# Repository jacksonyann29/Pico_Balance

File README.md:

# Pico_Balance
General Purpose Robot PCB with 2 motor drivers, IMU and appropriate power management for 9-24v. Intended to be used standalone or alongside an SBC depending on robotics application.

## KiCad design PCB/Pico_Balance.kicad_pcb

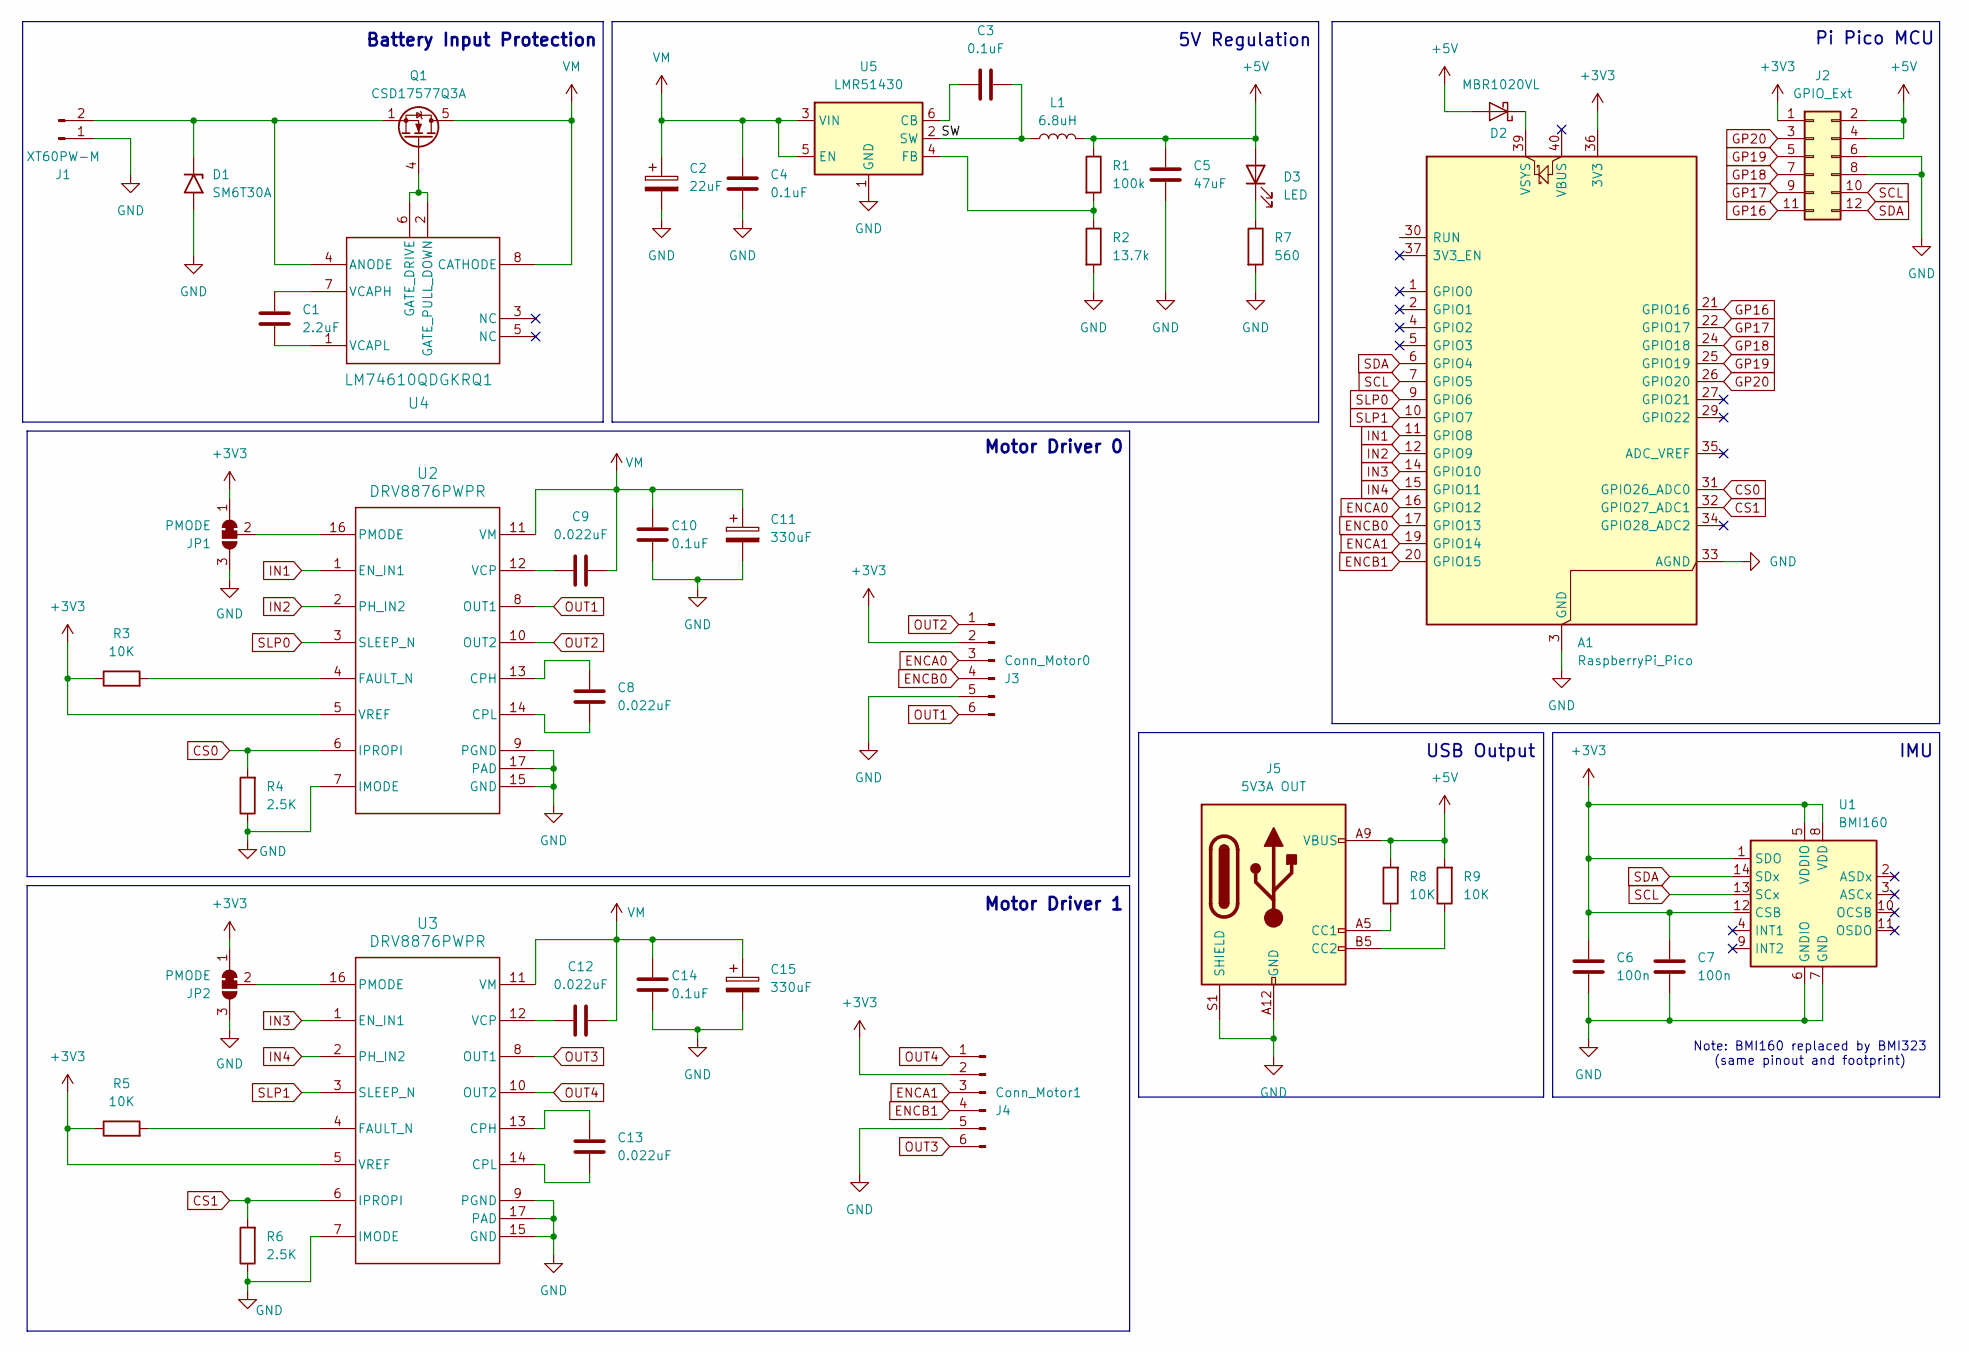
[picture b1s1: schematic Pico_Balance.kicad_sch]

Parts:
A1: RaspberryPi_Pico; RaspberryPi_Pico_Common_Unspecified
C1: 2.2uF; C_1206_3216Metric
C2: 22uF; CP_Elec_5x5.4
C3, C4, C10, C14: 0.1uF; C_0603_1608Metric
C5: 47uF; C_1210_3225Metric
C6, C7: 100n; C_0603_1608Metric
C8, C9, C12, C13: 0.022uF; C_0603_1608Metric
C11, C15: 330uF; CP_Elec_10x10.5
D1: SM6T30A; D_SMB
D2: MBR1020VL; D_SOD-123F
D3: LED; LED_0805_2012Metric
J1: XT60PW-M; AMASS_XT60PW-M_1x02_P7.20mm_Horizontal
J2: GPIO_Ext; PinHeader_2x06_P2.54mm_Vertical
J3: Conn_Motor0; PinSocket_1x06_P2.54mm_Vertical
J4: Conn_Motor1; PinSocket_1x06_P2.54mm_Vertical
J5: 5V3A OUT; USB_C_Receptacle_HRO_TYPE-C-31-M-17
JP1, JP2: PMODE; SolderJumper-3_P1.3mm_Bridged12_Pad1.0x1.5mm_NumberLabels
L1: 6.8uH; L_APV_APH0630
Q1: CSD17577Q3A; VSON-8_3.3x3.3mm_P0.65mm_NexFET
R1: 100k; R_0603_1608Metric
R2: 13.7k; R_0603_1608Metric
R3, R5, R8, R9: 10K; R_0603_1608Metric
R4, R6: 2.5K; R_0603_1608Metric
R7: 560; R_0603_1608Metric
U1: BMI160; Bosch_LGA-14_3x2.5mm_P0.5mm
U2, U3: DRV8876PWPR; PWP0016J_N
U4: LM74610QDGKRQ1; DGK0008A_N
U5: LMR51430; SOT-23-6

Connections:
+3V3: A1.36 (3V3), C6.1, C7.1, J2.1, J3.2, J4.2, JP1.1 (A), JP2.1 (A), R3.1, R5.1, U1.1 (SDO), U1.5 (VDDIO), U1.8 (VDD), U1.12 (CSB), U2.5 (VREF), U3.5 (VREF)
+5V: C5.1, D2.2 (A), D3.2 (A), J2.2, J2.4, J5.A9 (VBUS), J5.B9 (VBUS), L1.2, R1.1, R8.2, R9.2
/SW: C3.2, L1.1, U5.2 (SW)
CS0: A1.31 (GPIO26_ADC0), R4.2, U2.6 (IPROPI)
CS1: A1.32 (GPIO27_ADC1), R6.2, U3.6 (IPROPI)
ENCA0: A1.16 (GPIO12), J3.3
ENCA1: A1.19 (GPIO14), J4.3
ENCB0: A1.17 (GPIO13), J3.4
ENCB1: A1.20 (GPIO15), J4.4
GND: A1.3 (GND), A1.8 (GND), A1.13 (GND), A1.18 (GND), A1.23 (GND), A1.28 (GND), A1.33 (AGND), A1.38 (GND), C2.2, C4.2, C5.2, C6.2, C7.2, C10.2, C11.2, C14.2, C15.2, D1.2 (A2), J1.1, J2.6, J2.8, J3.5, J4.5, J5.A12 (GND), J5.B12 (GND), J5.S1 (SHIELD), JP1.3 (B), JP2.3 (B), R2.2, R4.1, R6.1, R7.2, U1.6 (GNDIO), U1.7 (GND), U2.7 (IMODE), U2.9 (PGND), U2.15 (GND), U2.17 (PAD), U3.7 (IMODE), U3.9 (PGND), U3.15 (GND), U3.17 (PAD), U5.1 (GND)
GP16: A1.21 (GPIO16), J2.11
GP17: A1.22 (GPIO17), J2.9
GP18: A1.24 (GPIO18), J2.7
GP19: A1.25 (GPIO19), J2.5
GP20: A1.26 (GPIO20), J2.3
IN1: A1.11 (GPIO8), U2.1 (EN_IN1)
IN2: A1.12 (GPIO9), U2.2 (PH_IN2)
IN3: A1.14 (GPIO10), U3.1 (EN_IN1)
IN4: A1.15 (GPIO11), U3.2 (PH_IN2)
unnamed: A1.39 (VSYS), D2.1 (K)
unnamed: D1.1 (A1), J1.2, Q1.1 (S), Q1.2 (S), Q1.3 (S), U4.4 (ANODE)
unnamed: D3.1 (K), R7.1
unnamed: J5.A5 (CC1), R8.1
unnamed: J5.B5 (CC2), R9.1
unnamed: JP1.2 (C), U2.16 (PMODE)
unnamed: JP2.2 (C), U3.16 (PMODE)
unnamed: Q1.4 (G), U4.2 (GATE_PULL_DOWN), U4.6 (GATE_DRIVE)
unnamed: C8.1, U2.13 (CPH)
unnamed: C8.2, U2.14 (CPL)
unnamed: R3.2, U2.4 (FAULT_N)
unnamed: C9.1, U2.12 (VCP)
unnamed: C13.1, U3.13 (CPH)
unnamed: C13.2, U3.14 (CPL)
unnamed: R5.2, U3.4 (FAULT_N)
unnamed: C12.1, U3.12 (VCP)
unnamed: C1.1, U4.7 (VCAPH)
unnamed: C1.2, U4.1 (VCAPL)
unnamed: C3.1, U5.6 (CB)
unnamed: R1.2, R2.1, U5.4 (FB)
OUT1: J3.6, U2.8 (OUT1)
OUT2: J3.1, U2.10 (OUT2)
OUT3: J4.6, U3.8 (OUT1)
OUT4: J4.1, U3.10 (OUT2)
SCL: A1.7 (GPIO5), J2.10, U1.13 (SCx)
SDA: A1.6 (GPIO4), J2.12, U1.14 (SDx)
SLP0: A1.9 (GPIO6), U2.3 (SLEEP_N)
SLP1: A1.10 (GPIO7), U3.3 (SLEEP_N)
VM: C2.1, C4.1, C9.2, C10.1, C11.1, C12.2, C14.1, C15.1, Q1.5 (D), U2.11 (VM), U3.11 (VM), U4.8 (CATHODE), U5.3 (VIN), U5.5 (EN)

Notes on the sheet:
Motor Driver 0
5V Regulation
USB Output
Pi Pico MCU
Note: BMI160 replaced by BMI323 (same pinout and footprint)
Motor Driver 1
IMU
Battery Input Protection

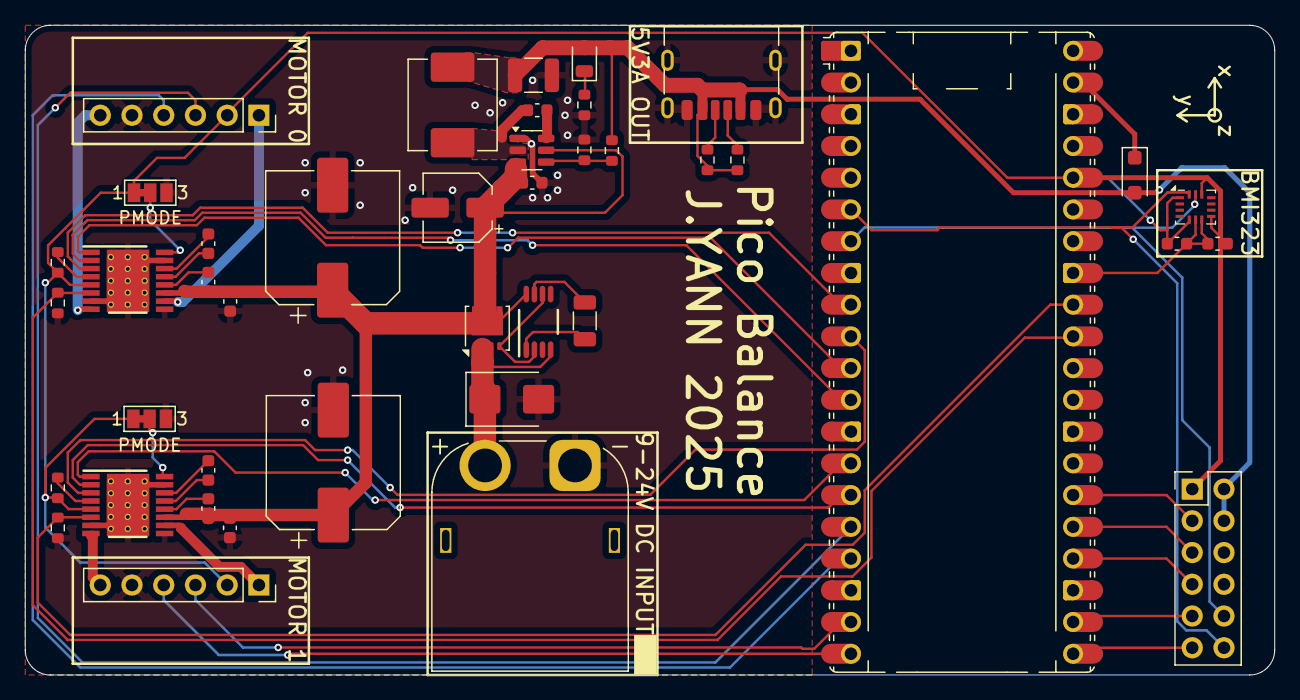
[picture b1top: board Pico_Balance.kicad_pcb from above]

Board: 2 copper layers, 100.0 x 52.0 mm, 42 parts (0 on the bottom side), 48 nets.

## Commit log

2025-06-21 Some initial Component Placement
2025-06-22 Power and IMU Layout
2025-06-22 Initial Motor Drive Layout
2025-06-25 Most component values assigned
2025-07-01 Add TVS Diode
2025-07-01 Second Motor Driver on Schematic
2025-07-03 Schematic Refinement and some footprint assignment
2025-07-03 Footprint Assignment
2025-07-03 Very Initial Layout and footprint updates
2025-07-04 Initial Input Protection Layout
2025-07-04 Layout Refinements and add USB C port for power
2025-07-04 Layout Refinements
2025-07-05 First Round of Routing
2025-07-05 routing!!!!
2025-07-06 Routing refinement and pour ground planes
2025-07-06 Link vias to ground plane
2025-07-06 Small refinements
2025-07-08 Silkscreen and minor layout changes
2025-07-08 Refinements
2025-07-09 Bigger Drill Vias for JLC tolerance, also more current?
2025-07-09 minor silkscreen and drc error correction
2025-07-09 improve routing around switching regulator
2025-07-23 Minor Silkscreen Adjustments
2025-07-23 Adjust MOSFET Footprint
2025-07-23 Generate Gerber and BOM
2025-08-22 Update Pins testing so it works on PCB
